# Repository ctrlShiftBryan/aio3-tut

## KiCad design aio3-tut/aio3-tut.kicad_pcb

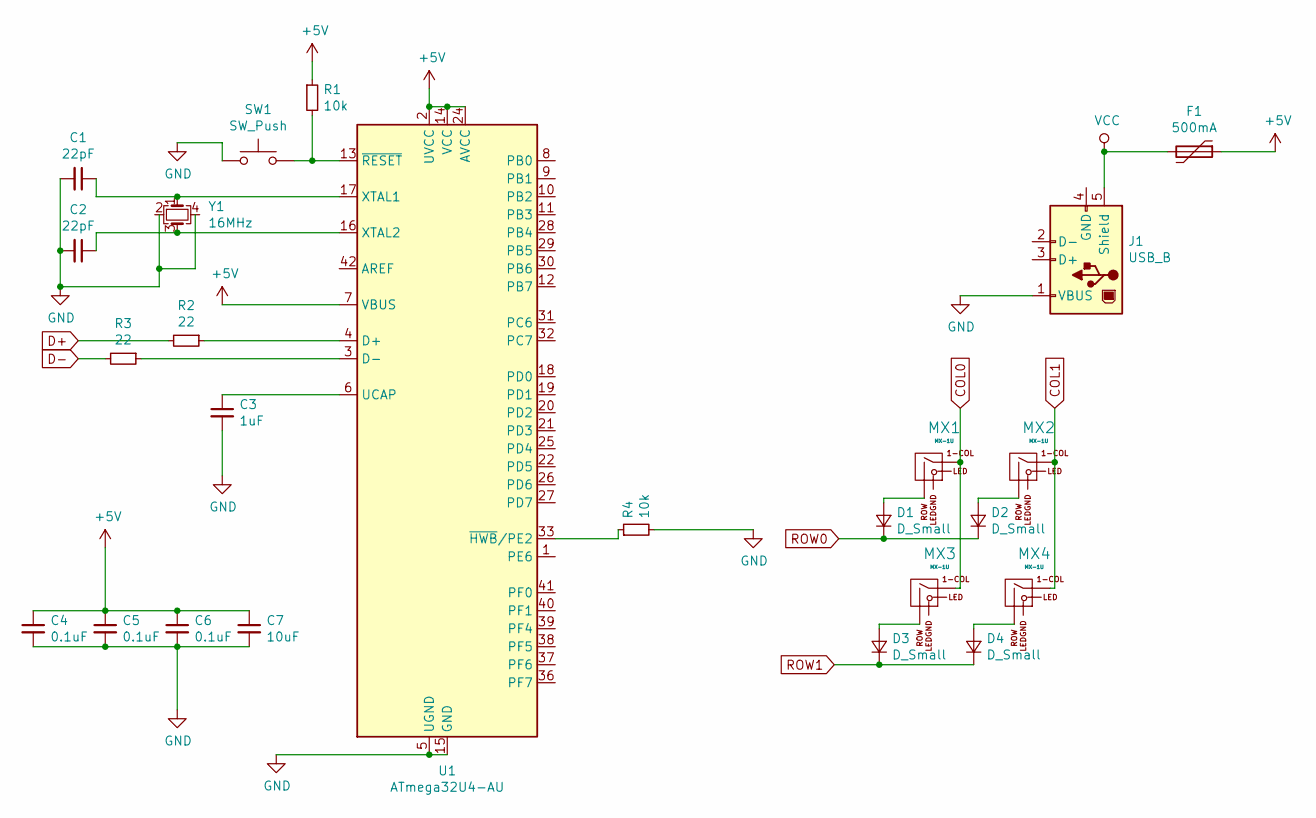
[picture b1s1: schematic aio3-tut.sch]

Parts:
C1, C2: 22pF; C_0805_2012Metric_Pad1.15x1.40mm_HandSolder
C3: 1uF; C_0805_2012Metric_Pad1.15x1.40mm_HandSolder
C4, C5, C6: 0.1uF; C_0805_2012Metric_Pad1.15x1.40mm_HandSolder
C7: 10uF; C_0805_2012Metric_Pad1.15x1.40mm_HandSolder
D1, D2, D3, D4: D_Small; D_SOD-123
F1: 500mA; Fuse_SMD1206_HandSoldering
J1: USB_B; Molex-0548190589
MX1, MX2, MX3, MX4: MX-1U
R1, R4: 10k; R_0805_2012Metric_Pad1.15x1.40mm_HandSolder
R2, R3: 22; R_0805_2012Metric_Pad1.15x1.40mm_HandSolder
SW1: SW_Push; SKQG-1155865
U1: ATmega32U4-AU; TQFP-44_10x10mm_Pitch0.8mm
Y1: 16MHz; Crystal_SMD_3225-4Pin_3.2x2.5mm

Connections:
+5V: C4.1, C5.1, C6.1, C7.1, F1.1, R1.1, U1.2 (UVCC), U1.7 (VBUS), U1.14 (VCC), U1.24 (AVCC), U1.34 (VCC), U1.44 (AVCC)
COL0: MX1.1 (COL), MX3.1 (COL)
COL1: MX2.1 (COL), MX4.1 (COL)
D+: R2.2
D-: R3.2
GND: C1.2, C2.2, C3.2, C4.2, C5.2, C6.2, C7.2, J1.1 (VBUS), R4.2, SW1.1, U1.5 (UGND), U1.15 (GND), U1.23 (GND), U1.35 (GND), U1.43 (GND)
unnamed: C1.1, U1.17 (XTAL1), Y1.1
unnamed: C2.1, U1.16 (XTAL2), Y1.3
unnamed: C3.1, U1.6 (UCAP)
unnamed: D1.2 (A), MX1.2 (ROW)
unnamed: D2.2 (A), MX2.2 (ROW)
unnamed: D3.2 (A), MX3.2 (ROW)
unnamed: D4.2 (A), MX4.2 (ROW)
unnamed: R1.2, SW1.2, U1.13 (~RESET)
unnamed: R2.1, U1.4 (D+)
unnamed: R3.1, U1.3 (D-)
unnamed: R4.1, U1.33 (~HWB~/PE2)
ROW0: D1.1 (K), D2.1 (K)
ROW1: D3.1 (K), D4.1 (K)
VCC: F1.2, J1.5 (Shield)

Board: 2 copper layers, 24 parts (20 on the bottom side), 18 nets, no tracks yet.

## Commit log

2019-04-20 init
2019-04-20 add submodules
2019-04-20 add librariers
2019-04-21 create schematic
2019-04-22 schematic footprints done
2019-04-22 fixes
2019-04-23 placed
